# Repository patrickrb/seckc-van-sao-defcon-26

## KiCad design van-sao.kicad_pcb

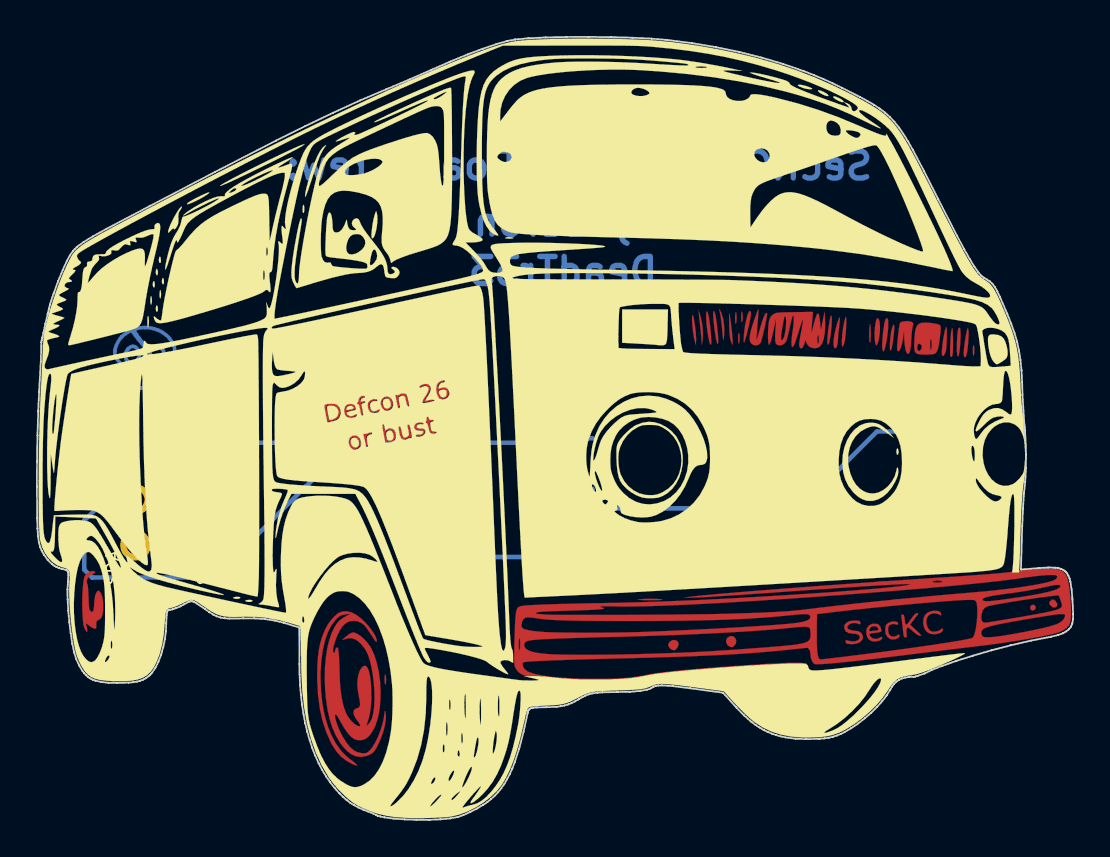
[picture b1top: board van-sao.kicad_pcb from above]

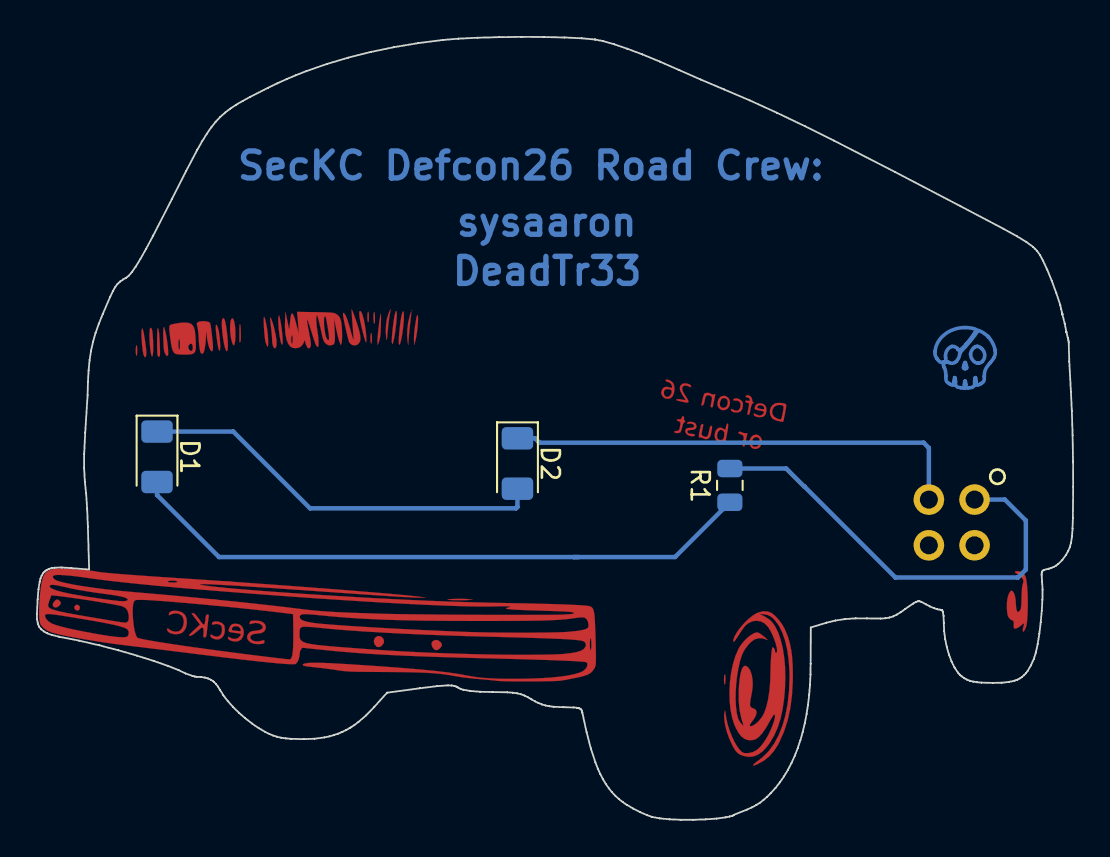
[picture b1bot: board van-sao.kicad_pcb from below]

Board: 2 copper layers, 57.6 x 43.5 mm, 4 parts (4 on the bottom side), 4 nets.

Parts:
D1, D2: LED; LED_1206_3216Metric
R1: 1K; R_0805_2012Metric
X1: Badgelife_shitty_connector; Badgelife-Shitty-2x2

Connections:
unnamed: D1.1, D2.2
unnamed: D1.2, R1.1
unnamed: D2.1, X1.2
unnamed: R1.2, X1.1

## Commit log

2019-05-10 need to change LEDS and rework logos
2019-05-14 getting svg2shenzen artwork implemented
2019-05-14 updated gerbers for new art
2019-05-18 final for first production run
